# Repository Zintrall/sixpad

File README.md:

# sixpad
Sixpad is a simple macropad with six switches, rotary encoder and a OLED display

## Features
- 128x32 OLED Display
- EC11 Rotary encoder
- 6 Keys
- RP2040
- VIAL support

## PCB
- designed using KiCAD

## Case
- designed using openSCAD

The case is only one part, as the PCB will be put in place through the bottom hole and held there by 4x M3 nuts and screws.

## Firmware
- uses QMK firmware
- supports vial (even rotary encoder)
- OLED display displays what layer you are on

## BOM
- 6x Cherry MX Switches
- 6x DSA Keycaps
- 4x M3x16mm SHCS Bolts
- 4x M3 Nuts
- 6x 1N4148 DO-35 Diodes.
- 1x 0.91" 128x32 OLED Display
- 1x EC11 Rotary Encoder
- 1x XIAO RP2040
- 1x Case

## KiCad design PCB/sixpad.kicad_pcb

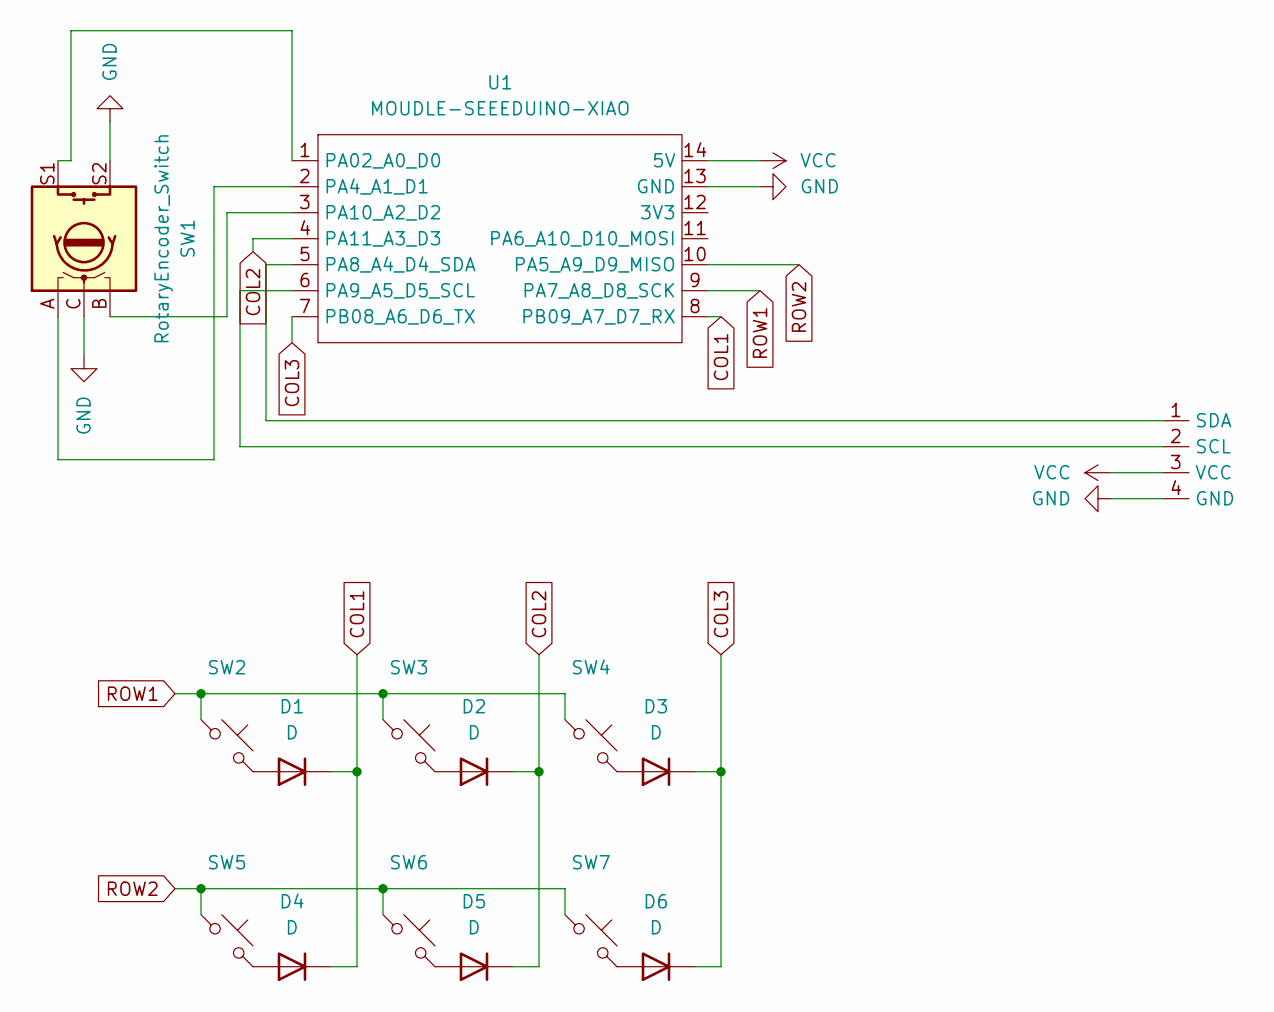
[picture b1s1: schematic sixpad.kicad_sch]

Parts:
D1, D2, D3, D4, D5, D6: D; D_DO-35_SOD27_P7.62mm_Horizontal
OLED1: PinHeader_1x04_P2.54mm_Vertical
SW1: RotaryEncoder_Switch; RotaryEncoder_Alps_EC11E-Switch_Vertical_H20mm
SW2, SW3, SW4, SW5, SW6, SW7: SW_Push_45deg; SW_Cherry_MX_1.00u_PCB
U1: MOUDLE-SEEEDUINO-XIAO; XIAO-Generic-Hybrid-14P-2.54-21X17.8MM

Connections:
COL1: D1.1 (K), D4.1 (K), U1.8 (PB09_A7_D7_RX)
COL2: D2.1 (K), D5.1 (K), U1.4 (PA11_A3_D3)
COL3: D3.1 (K), D6.1 (K), U1.7 (PB08_A6_D6_TX)
GND: OLED1.4 (GND), SW1.C, SW1.S2, U1.13 (GND)
unnamed: D1.2 (A), SW2.2
unnamed: D2.2 (A), SW3.2
unnamed: D3.2 (A), SW4.2
unnamed: D4.2 (A), SW5.2
unnamed: D5.2 (A), SW6.2
unnamed: D6.2 (A), SW7.2
unnamed: OLED1.2 (SCL), U1.6 (PA9_A5_D5_SCL)
unnamed: OLED1.1 (SDA), U1.5 (PA8_A4_D4_SDA)
unnamed: SW1.S1, U1.1 (PA02_A0_D0)
unnamed: SW1.A, U1.2 (PA4_A1_D1)
unnamed: SW1.B, U1.3 (PA10_A2_D2)
ROW1: SW2.1, SW3.1, SW4.1, U1.9 (PA7_A8_D8_SCK)
ROW2: SW5.1, SW6.1, SW7.1, U1.10 (PA5_A9_D9_MISO)
VCC: OLED1.3 (VCC), U1.14 (5V)

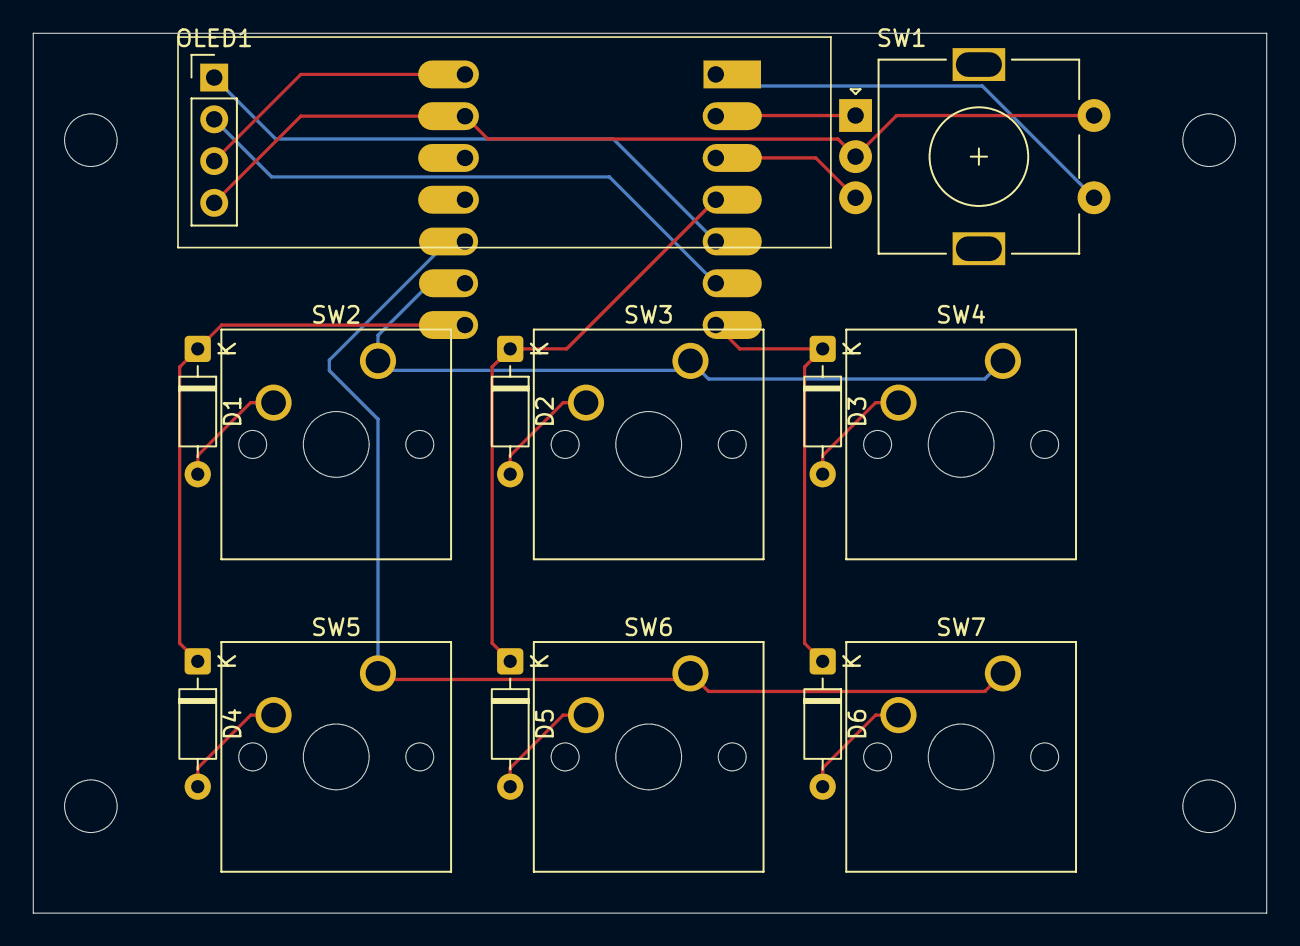
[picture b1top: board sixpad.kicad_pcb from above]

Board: 2 copper layers, 75.0 x 53.5 mm, 15 parts (1 on the bottom side), 18 nets.

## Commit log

2026-02-23 Project upload
2026-02-24 Fixed the PCB image so it shows up
2026-02-24 renamed pcb.png
2026-02-24 added 3D PCB image
2026-02-25 Fixed gbrjob file
2026-03-11 updated 3D models
2026-04-01 Added basic vial support
2026-04-04 fixed vial
2026-04-04 resized usb-c case slot
2026-04-04 fixed the display
2026-04-04 updated images
